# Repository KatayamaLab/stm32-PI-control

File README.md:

# nucleo-impedance-analyzer

nucleo-imzepedance-analyzer is a tiny impedance analyzer for such as lithium-ion batteries to  measure impedance data. It features

- Uses NUCLEO microcontroller board manufactured by ST Microelectronics
- Includes charge/discharge module that can be detached.

## Requirements

The following is an install guide for Visual Studio.

**MacOS**

1. Install OpenOCD (**Only 0.11.0 is acceptable. Version 0.12.0 and newer does not work.**) using the following command `brew install openocd` *For Apple Silicon, x64 version is requred* 
2. Install GCC ARM Toolchain. First, `brew tap osx-cross/arm & brew install arm-gcc-bin` (https://github.com/osx-cross/homebrew-arm)
3. Download STM32Cube Initialization code generator from [ST Microelectronics STM32 Cube MX](https://www.st.com/en/development-tools/stm32cubemx.html) and install it. (6.5.0 or above is recommended)
4.  Install Cortex-Debug extension (Search in Visual Studio Code)
5. Specify `cortex-debug.armToolchainPath` in setting of visual studio code to the path specified in `which arm-none-eabi-gdb`
6. Install `Draw.io` Integration extention to VS Code
7. Install unit-test framework `brew install cpputest`.
8. If using intel mac, `sudo mkdir /opt/homebrew/opt && ln -s /usr/local/Celler/cpputest/4.0 /opt/homebrew/opt/cpputest`

**Windows**

1. Download and install OpenOCD from https://gnutoolchains.com/arm-eabi/openocd/
2. Download Install GCC ARM Toolchain from https://developer.arm.com/tools-and-software/open-source-software/developer-tools/gnu-toolchain/gnu-rm/downloads and install it.
3. Download STM32Cube Initialization code generator from [ST Microelectronics STM32 Cube MX](https://www.st.com/en/development-tools/stm32cubemx.html) and install it. (6.5.0 or above is recommended)
4. Install Cortex-Debug extension (Search in Visual Studio Code)
5. Specify `cortex-debug.armToolchainPath` in setting of visual studio code to the path specified in `which arm-none-eabi-gdb`
6. Install `Draw.io` Integration extiontion to VS Code
4. Download [Make for Windows](http://gnuwin32.sourceforge.net/packages/make.htm) and set the bin file path to environmental variables or temporally add it to PATH in step 6.
5. Install `Cortex-Debug` and `Draw.io Integration` extension(Search in Visual Studio Code)
6. Add json files and configure(refer to startup.txt in Document).

## Peripheral Customization
To modify peripheral settings (for example, pin settings), use STM32 CubeMX and open `app.ioc`

## How to run

Run -> Start Debugging

## Specification

- 要望
  - 1000mAh程度のリチウムイオン電池のインピーダンスが測定できる
  - 100mHz〜10kHzで測定可能
  - できれば電圧振幅で与えたい。5mV程度
  - たぶん難しいので電流振幅で与える
  - ★なるべく小さくしたい
  - ★リチウムイオン電池で駆動させたい
    - どうしても電流を消費して外乱になってしまうので，少し大きめのコンデンサを取り付ける。
    - 平衡電位では無理
  - 充放電機能はまだ不要ということなので，片山研的にはほしいので，切り離せるように設計する。

- 具体的仕様
  - Frequency 100mHz-10kHz
  - AC Voltage 33mVpp
  - AC Current 165mApp
  - DC Voltage 2.5-4.5V
  - DC Current +- 1.0A

## Microcontroller STM32F303K8
- K8は32-pin LQFP
- 72MHz
- Flash 64kB, RAM 16kB  (2byte(12bit) x 1024 x {(voltage, current) x (real, imag) +1} = 9kB)
- 2 x 12-bit DACs
- 4x 12bit-ADCs 5MSPS
    - 10kHzなら500サンプル
    - AC用・DC用・直流キャンセル用（電流・電圧）でちょうど使える
## Pin asign

Nucleo
|    # | Nucleo | STM32 | Description                | function                                    |
| ---: | :----: | :---: | :------------------------- | :------------------------------------------ |
|    1 | D1/TX  |  PA9  | UART1_TX                   |                                             |
|    2 | D0/TR  | PA10  | UART1_RX                   |                                             |
|    3 |  RST   | NRST  |                            |                                             |
|    4 |  GNT   |  GND  |                            |                                             |
|    5 |   D2   | PA12  |                            |                                             |
|    6 |   D3   |  PB0  | (TIM3_CH3)                 |                                             |
|    7 |   D4   |  PB7  | (connected to A4 via SB18) |                                             |
|    8 |   D5   |  PB6  | (connected to A5 via SB16) |                                             |
|    9 |   D6   |  PB1  | (TIM3_CH4)                 |                                             |
|   10 |   D7   |  PF0  | (XTAL)                     |                                             |
|   11 |   D8   |  PF1  | (XTAL)                     |                                             |
|   12 |   D9   |  PA8  | (TIM1_CH1)                 |                                             |
|   13 |  D10   | PA11  | (SPI_CS, TIM1_CH4)         |                                             |
|   14 |  D11   |  PB5  | (SPI_MOSI, TIM17_CH1)      |                                             |
|   15 |  D12   |  PB4  | (SPI1_MISO)                |                                             |
|    - |   -    |       |                            |                                             |
|    1 |  VIN   |       |                            |                                             |
|    2 |  GND   |       |                            |                                             |
|    3 |  RST   |       |                            |                                             |
|    4 |   5V   |       |                            |                                             |
|    5 |   A7   |  PA2  |                            |                                             |
|    6 |   A6   |  PA7  | ADC2_IN4                   |                                             |
|    7 |   A5   |  PA6  | DAC2_OUT1                  | sine wave (on-demand) (connected to D5)     |
|    8 |   A4   |  PA5  | DAC1_OUT2                  | triangle wave (on-demand) (connected to D4) |
|    9 |   A3   |  PA4  | DAC1_OUT1                  |                                             |
|   10 |   A2   |  PA3  | ADC1_IN4                   |                                             |
|   11 |   A1   |  PA1  | ADC1_IN2                   |                                             |
|   12 |   A0   |  PA0  | ADC1_IN1                   |                                             |
|   13 |  AREF  |       |                            | ****                                        |
|   14 |  +3.3  |       |                            |
|   15 |  D13   |  PB3  | GPIO/NUCLEO LED            |

# Reference
[Sallen-key fillter](http://sim.okawa-denshi.jp/Sallen3tool.php)

https://github.com/KatayamaLab/IDA/blob/master/pcb_3_1/board_a.sch.pdf
https://github.com/KatayamaLab/IDA/blob/master/pcb_3_1/board_b.sch.pdf

# Parts
CRCW08051R00FKEAHP 1Ω, 0805 (2012M), 0.5W, ±1%
https://jp.rs-online.com/web/p/surface-mount-fixed-resistors/8123460
TLM3AER01FTE , 10mΩ, 2512 (6432M), 1W, ±1
power amp, AD8531AKSZ,
https://jp.rs-online.com/web/p/op-amps/9140309

# Datasheets
片山研究室・共有フォルダ/1_研究データ/2022_LIB_EIS_ML/リチウムイオン電池測定基板/部品データシート
https://tus.box.com/s/zwcsuqmixppwy6xl2a2gfuegczw5wa8e

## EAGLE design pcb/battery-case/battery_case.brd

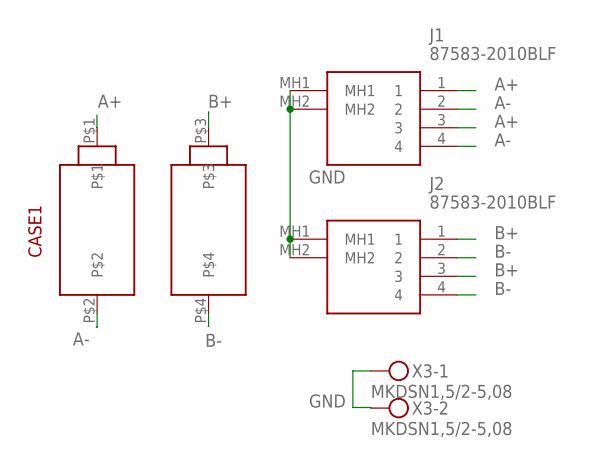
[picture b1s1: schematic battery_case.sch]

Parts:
CASE1: BATTERY_CASE; CASE
J1, J2: 87583-2010BLF; 875832010BLF
X3: MKDSN1,5/2-5,08

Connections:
A+: CASE1.P$1, J1.1, J1.3
A-: CASE1.P$2, J1.2, J1.4
B+: CASE1.P$3, J2.1, J2.3
B-: CASE1.P$4, J2.2, J2.4
GND: J1.MH1, J1.MH2, J2.MH1, J2.MH2, X3.1, X3.2

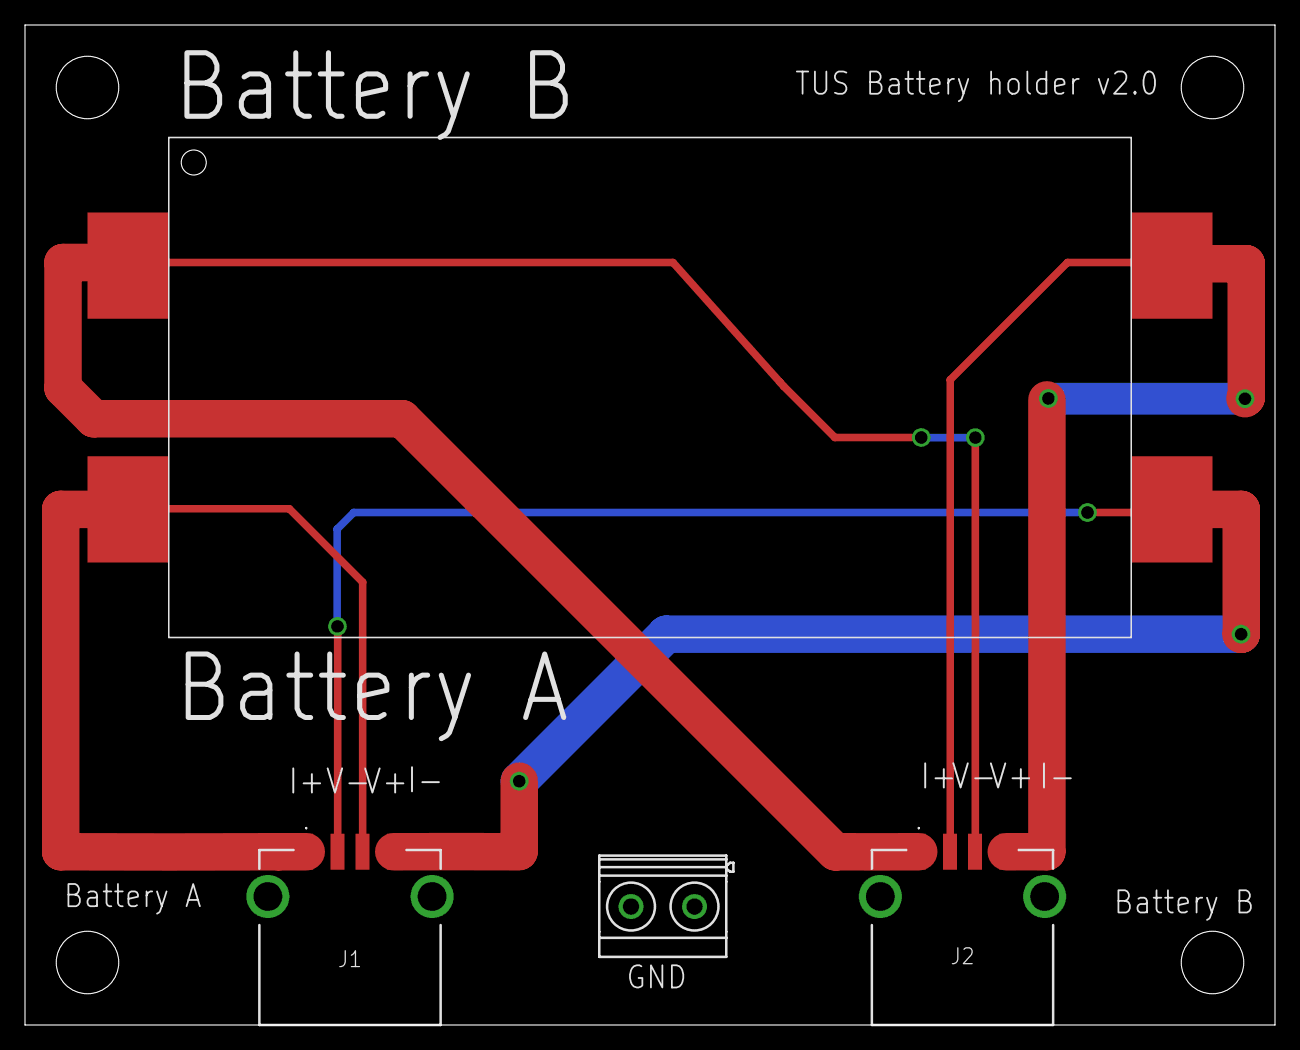
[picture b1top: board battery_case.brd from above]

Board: 2 copper layers, 100.0 x 80.0 mm, 4 parts (0 on the bottom side), 5 nets.

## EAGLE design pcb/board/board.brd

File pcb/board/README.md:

# nucleo-impeance-analyzer

# Environment

- VS Code
  - Draw.io Integraton

# Specification

- DC
  - Voltage 2.5-4.5 V (Nominal 3.6V)
  - Current +-2 A
    - shunt 10mR >> 50mA >> 250mW
- AC
  - Voltage 100 mVp-p (0.05-2 Ohm)
    - Amp
      1. x10
      2. x10
      3. x1 (LPF)
  - Current 50 mAp-p
    - Shunt Resistance 10R >> 500mV
  - Frequency 1 mHz-10 kHz
  -

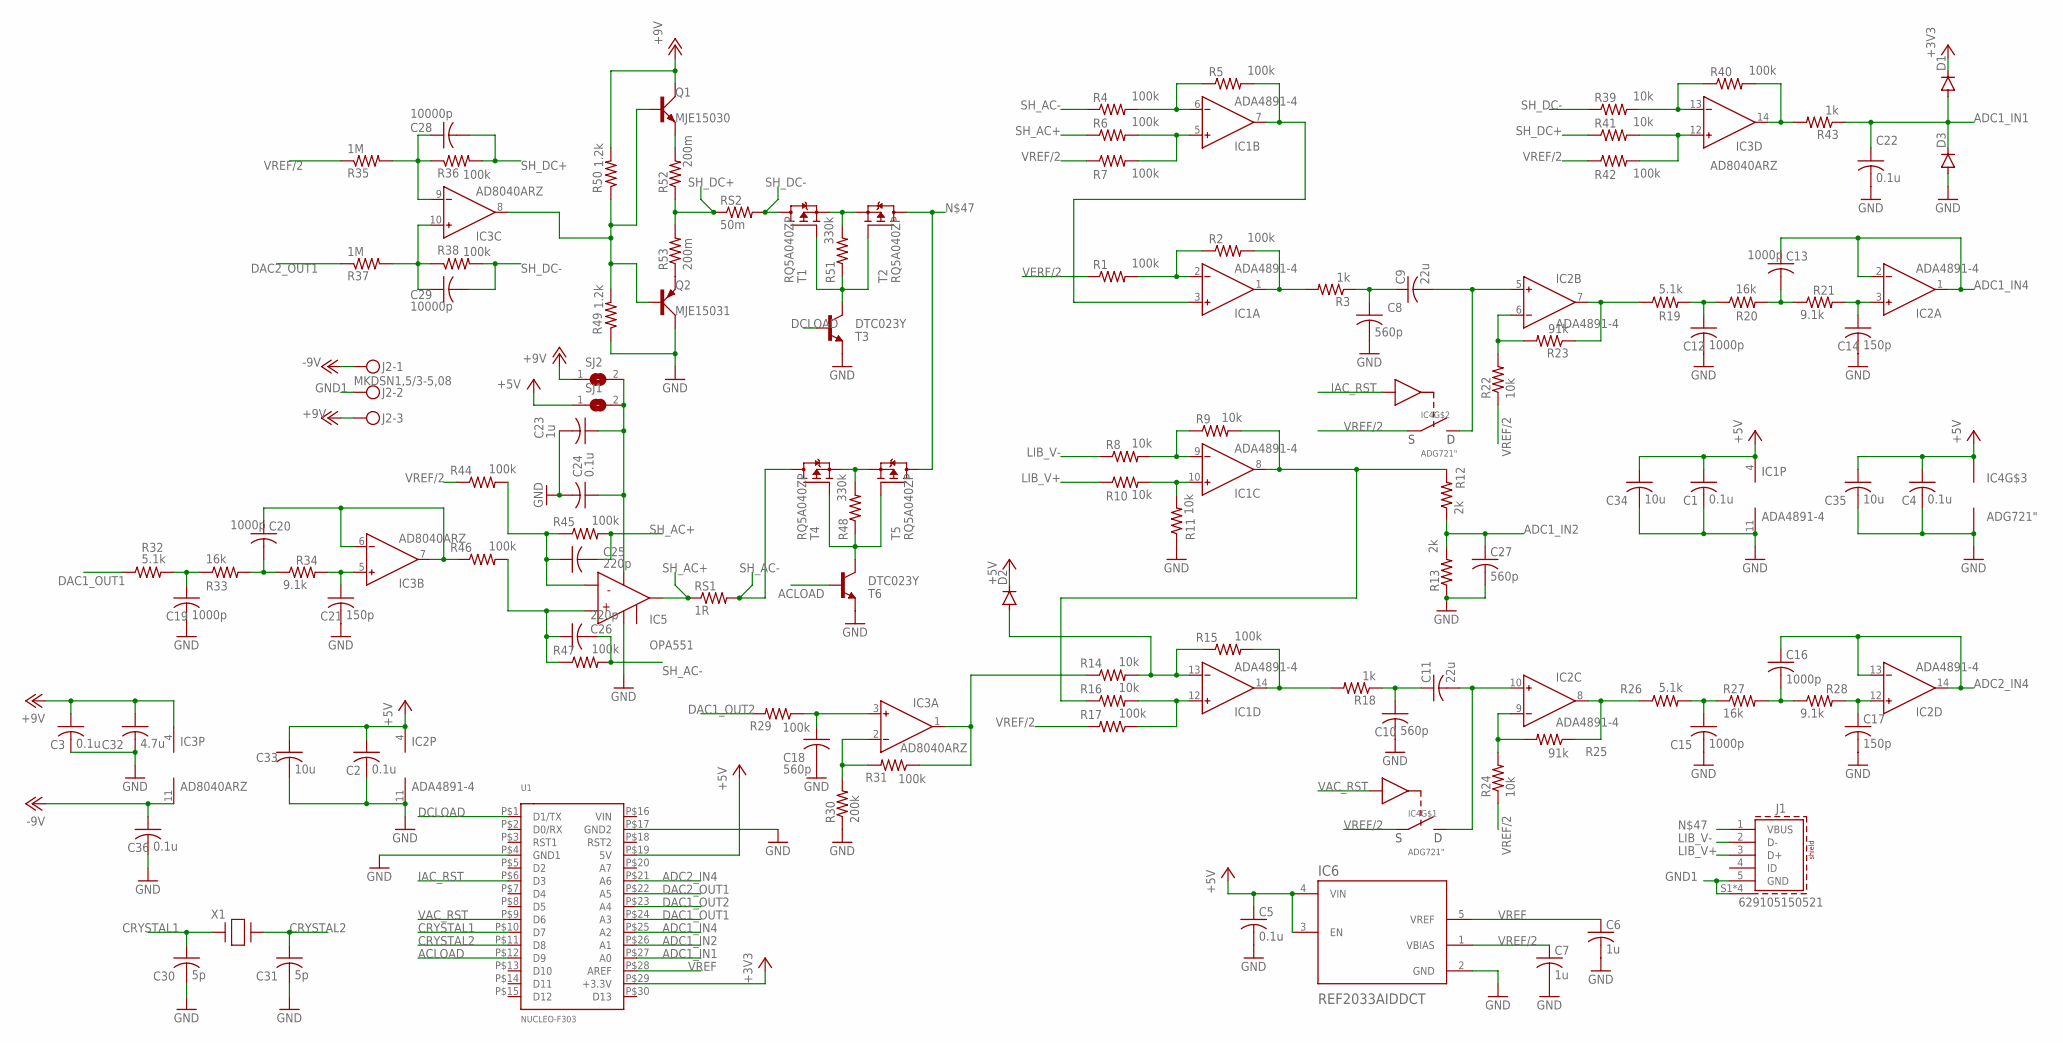
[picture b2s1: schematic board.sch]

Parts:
C1, C2, C3, C4, C5, C22, C24, C36: 0.1u; C0402K
C6, C7, C23: 1u; C0402K
C8, C10, C18, C27: 560p; C0402K
C9, C11: 22u; C0805
C12, C13, C15, C16, C19, C20: 1000p; C0402K
C14, C17, C21: 150p; C0402K
C25, C26: 220p; C0402K
C28, C29: 10000p; C0402K
C30, C31: 5p; C0402K
C32: 4.7u; C0402K
C33, C34, C35: 10u; C0402K
D1, D2, D3: DIODE-SOD123; SOD123
IC1, IC2: ADA4891-4; SO14
IC3: AD8040ARZ; SO14
IC4: ADG721"; MSOP8
IC5: OPA551; TO127P1435X464-8N
IC6: REF2033AIDDCT; SOT95P280X110-5N
J1: 629105150521
J2: MKDSN1,5/3-5,08
Q1: MJE15030; TO220AV
Q2: MJE15031; TO220AV
R1, R2, R4, R5, R6, R7, R15, R17, R29, R31, R36, R38, R40, R42, R44, R45, R46, R47: 100k; R0402
R3, R18, R43: 1k; R0402
R8, R9, R10, R11, R14, R16, R22, R24, R39, R41: 10k; R0402
R12, R13: 2k; R0402
R19, R26, R32: 5.1k; R0402
R20, R27, R33: 16k; R0402
R21, R28, R34: 9.1k; R0402
R23, R25: 91k; R0402
R30: 200k; R0402
R35, R37: 1M; R0402
R48, R51: 330k; R0402
R49, R50: 1.2k; R0402
R52, R53: 200m; R2512
RS1: 1R; R2512
RS2: 50m; R2512
SJ1, SJ2: SJ
T1, T2, T4, T5: RQ5A040ZP; SOT23
T3, T6: DTC023Y; SOT40P120X55-3N
U1: NUCLEO-F303
X1: NX3225GD-8MHZ-STD-CRA-3XTAL_NX3225GD-8MHZ-STD-CRA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; XTAL_NX3225GD-8MHZ-STD-CRA-3_N

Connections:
+3V3: D1.C, U1.P$29 (+3.3V)
+5V: C1.1, C2.1, C4.1, C5.1, C33.1, C34.1, C35.1, D2.C, IC1.4 (V+), IC2.4 (V+), IC4.8 (VDD), IC6.3 (EN), IC6.4 (VIN), SJ1.1, U1.P$19 (5V)
+9V: J2.3, Q1.C, R50.2, SJ2.1
-9V: C36.1, IC3.11 (V-), J2.1
ACLOAD: T6.1 (B), U1.P$12 (D9)
ADC1_IN1: C22.1, D1.A, D3.C, R43.1, U1.P$27 (A0)
ADC1_IN2: C27.1, R12.1, R13.2, U1.P$26 (A1)
ADC1_IN3: IC3.1 (OUT), R14.1, R31.1
ADC1_IN4: C13.1, IC2.1 (OUT), IC2.2 (IN-), U1.P$25 (A2)
ADC2_IN4: C16.1, IC2.13 (IN-), IC2.14 (OUT), U1.P$21 (A6)
CRYSTAL1: C30.1, U1.P$10 (D7), X1.2
CRYSTAL2: C31.1, U1.P$11 (D8), X1.1
DAC1_OUT1: R32.1, U1.P$24 (A3)
DAC1_OUT2: R29.2, U1.P$23 (A4)
DAC2_OUT1: R37.1, U1.P$22 (A5)
DCLOAD: T3.1 (B), U1.P$1 (D1/TX)
GND1: C1.2, C2.2, C3.2, C4.2, C5.2, C6.2, C7.2, C8.2, C10.2, C12.2, C14.2, C15.2, C17.2, C18.2, C19.2, C21.2, C22.2, C23.2, C24.2, C27.2, C30.2, C31.2, C32.2, C33.2, C34.2, C35.2, C36.2, D3.A, IC1.11 (V-), IC2.11 (V-), IC4.4 (GND), IC5.4 (V-), IC5.8 (V-), IC6.2 (GND), J1.5 (GND), J1.S1 (SHIELD), J1.S2 (SHIELD), J1.S3 (SHIELD), J1.S4 (SHIELD), J2.2, Q2.C, R11.1, R13.1, R30.1, R49.1, T3.2 (E), T6.2 (E), U1.P$4 (GND1), U1.P$17 (GND2)
IAC_RST: IC4.3 (IN), U1.P$6 (D3)
LIB_V+: J1.3 (D+), R10.1
LIB_V-: J1.2 (D-), R8.1
unnamed: IC3.8 (OUT), Q1.B, Q2.B, R49.2, R50.1
unnamed: C16.2, R27.2, R28.1
unnamed: IC1.9 (IN-), R8.2, R9.1
unnamed: C9.2, IC2.5 (IN+), IC4.6 (D)
unnamed: IC1.14 (OUT), R15.2, R18.2
unnamed: C17.1, IC2.12 (IN+), R28.2
unnamed: C15.1, R26.2, R27.1
unnamed: IC2.8 (OUT), R25.1, R26.1
unnamed: IC2.9 (IN-), R24.2, R25.2
unnamed: C11.2, IC2.10 (IN+), IC4.2 (D)
unnamed: IC1.12 (IN+), R16.2, R17.1
unnamed: D2.A, IC1.13 (IN-), R14.2, R15.1
unnamed: IC3.13 (IN-), R39.2, R40.1
unnamed: IC3.12 (IN+), R41.2, R42.2
unnamed: IC1.10 (IN+), R10.2, R11.2
unnamed: IC1.6 (IN-), R4.2, R5.1
unnamed: IC1.5 (IN+), R6.2, R7.2
unnamed: C13.2, R20.2, R21.1
unnamed: IC3.2 (IN-), R30.2, R31.2
unnamed: C14.1, IC2.3 (IN+), R21.2
unnamed: C12.1, R19.2, R20.1
unnamed: IC2.6 (IN-), R22.2, R23.2
unnamed: IC2.7 (OUT), R19.1, R23.1
unnamed: Q2.E, R53.1
unnamed: IC1.3 (IN+), IC1.7 (OUT), R5.2
unnamed: R51.2, T1.2 (S), T2.2 (S)
unnamed: IC3.14 (OUT), R40.2, R43.2
unnamed: C26.1, IC5.1 (+IN), R46.2, R47.1
unnamed: C18.1, IC3.3 (IN+), R29.1
unnamed: C20.2, R33.2, R34.1
unnamed: C20.1, IC3.6 (IN-), IC3.7 (OUT), R46.1
unnamed: C21.1, IC3.5 (IN+), R34.2
unnamed: C19.1, R32.2, R33.1
unnamed: R51.1, T1.1 (G), T2.1 (G), T3.3 (C)
unnamed: IC1.2 (IN-), R1.2, R2.1
unnamed: C3.1, C23.1, C24.1, C32.1, IC3.4 (V+), IC5.5 (V+), SJ1.2, SJ2.2
unnamed: C29.1, IC3.10 (IN+), R37.2, R38.1
unnamed: C28.1, IC3.9 (IN-), R35.2, R36.1
unnamed: Q1.E, R52.2
unnamed: R48.2, T4.2 (S), T5.2 (S)
unnamed: IC1.1 (OUT), R2.2, R3.2
unnamed: C8.1, C9.1, R3.1
unnamed: C10.1, C11.1, R18.1
unnamed: R48.1, T4.1 (G), T5.1 (G), T6.3 (C)
unnamed: J1.1 (VBUS), T2.3 (D), T5.3 (D)
unnamed: IC1.8 (OUT), R9.2, R12.2, R16.1
unnamed: C25.1, IC5.2 (-IN), R44.2, R45.1
SH_AC+: C25.2, IC5.6 (OUT), R6.1, R45.2, RS1.1
SH_AC-: C26.2, R4.1, R47.2, RS1.2, T4.3 (D)
SH_DC+: C28.2, R36.2, R41.1, R52.1, R53.2, RS2.1
SH_DC-: C29.2, R38.2, R39.1, RS2.2, T1.3 (D)
VAC_RST: IC4.7 (IN), U1.P$9 (D6)
VERF/2: R1.1
VIN: U1.P$16 (VIN)
VREF: C6.1, IC6.5 (VREF), U1.P$28 (AREF)
VREF/2: C7.1, IC4.1 (S), IC4.5 (S), IC6.1 (VBIAS), R7.1, R17.2, R22.1, R24.1, R35.1, R42.1, R44.1

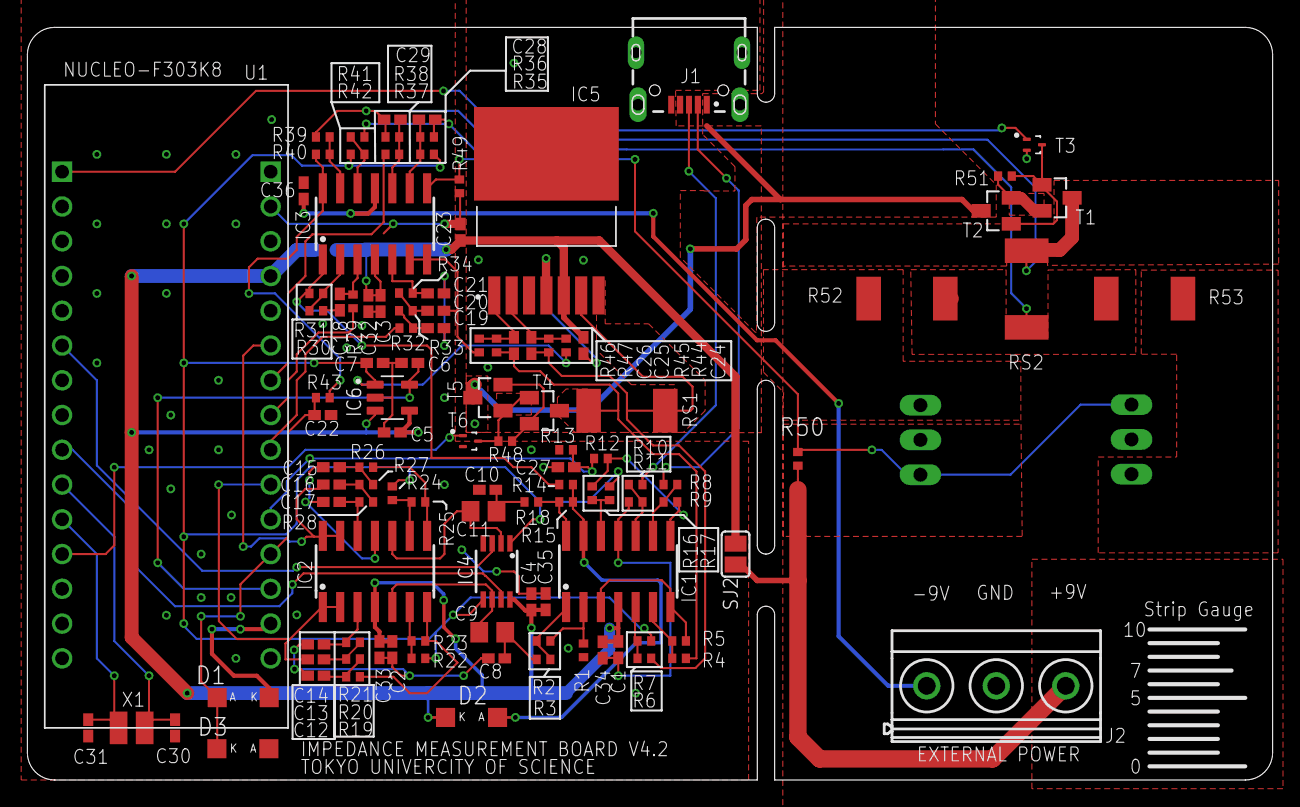
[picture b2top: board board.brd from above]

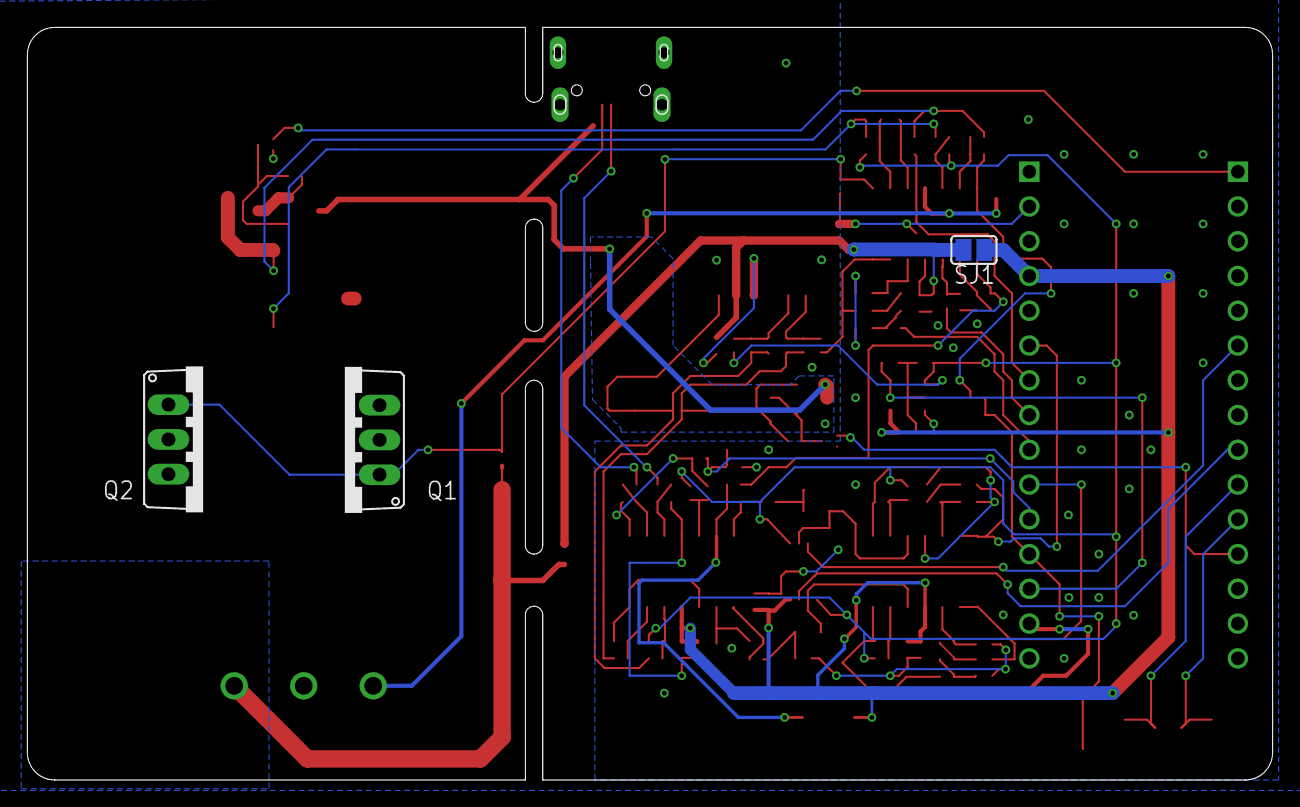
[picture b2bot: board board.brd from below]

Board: 2 copper layers, 91.0 x 55.0 mm, 114 parts (3 on the bottom side), 74 nets.

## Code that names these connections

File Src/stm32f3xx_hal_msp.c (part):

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
    __HAL_RCC_GPIOA_CLK_ENABLE();
    /**ADC1 GPIO Configuration
    PA1     ------> ADC1_IN2
    PA3     ------> ADC1_IN4
    */
    GPIO_InitStruct.Pin = GPIO_PIN_1|GPIO_PIN_3;
    GPIO_InitStruct.Mode = GPIO_MODE_ANALOG;
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
    __HAL_RCC_GPIOA_CLK_ENABLE();
    /**ADC2 GPIO Configuration
    PA7     ------> ADC2_IN4
    */
    GPIO_InitStruct.Pin = GPIO_PIN_7;
    GPIO_InitStruct.Mode = GPIO_MODE_ANALOG;
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    }

    /**ADC1 GPIO Configuration
    PA1     ------> ADC1_IN2
    PA3     ------> ADC1_IN4
    */
    HAL_GPIO_DeInit(GPIOA, GPIO_PIN_1|GPIO_PIN_3);

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    }

    /**ADC2 GPIO Configuration
    PA7     ------> ADC2_IN4
    */
    HAL_GPIO_DeInit(GPIOA, GPIO_PIN_7);

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
    __HAL_RCC_GPIOA_CLK_ENABLE();
    /**DAC1 GPIO Configuration
    PA5     ------> DAC1_OUT2
    */
    GPIO_InitStruct.Pin = GPIO_PIN_5;
    GPIO_InitStruct.Mode = GPIO_MODE_ANALOG;
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    __HAL_RCC_DAC1_CLK_DISABLE();

    /**DAC1 GPIO Configuration
    PA5     ------> DAC1_OUT2
    */
    HAL_GPIO_DeInit(GPIOA, GPIO_PIN_5);

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
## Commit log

2025-07-15 copy
2025-07-24 pi configuration
2025-07-30 enable gpio fast mode
2025-08-01 modify-bug

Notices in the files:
Src/stm32f3xx_hal_msp.c:
© Copyright (c) 2020 STMicroelectronics.
All rights reserved.
This software component is licensed by ST under BSD 3-Clause license,
the "License"; You may not use this file except in compliance with the
License. You may obtain a copy of the License at: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
parts and their libraries:
Wurth_Connectors_WR-USB-DrillSize-Modifi: Copyright: Würth Elektronik
COPYRIGHT: Copyright (C) 2022 Ultra Librarian. All rights reserved.
